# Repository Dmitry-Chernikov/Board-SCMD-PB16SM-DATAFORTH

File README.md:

# Board-SCMD-PB16SM-DATAFORTH
Board SCMD-PB16SM DATAFORTH modules MIDC5/MODC5

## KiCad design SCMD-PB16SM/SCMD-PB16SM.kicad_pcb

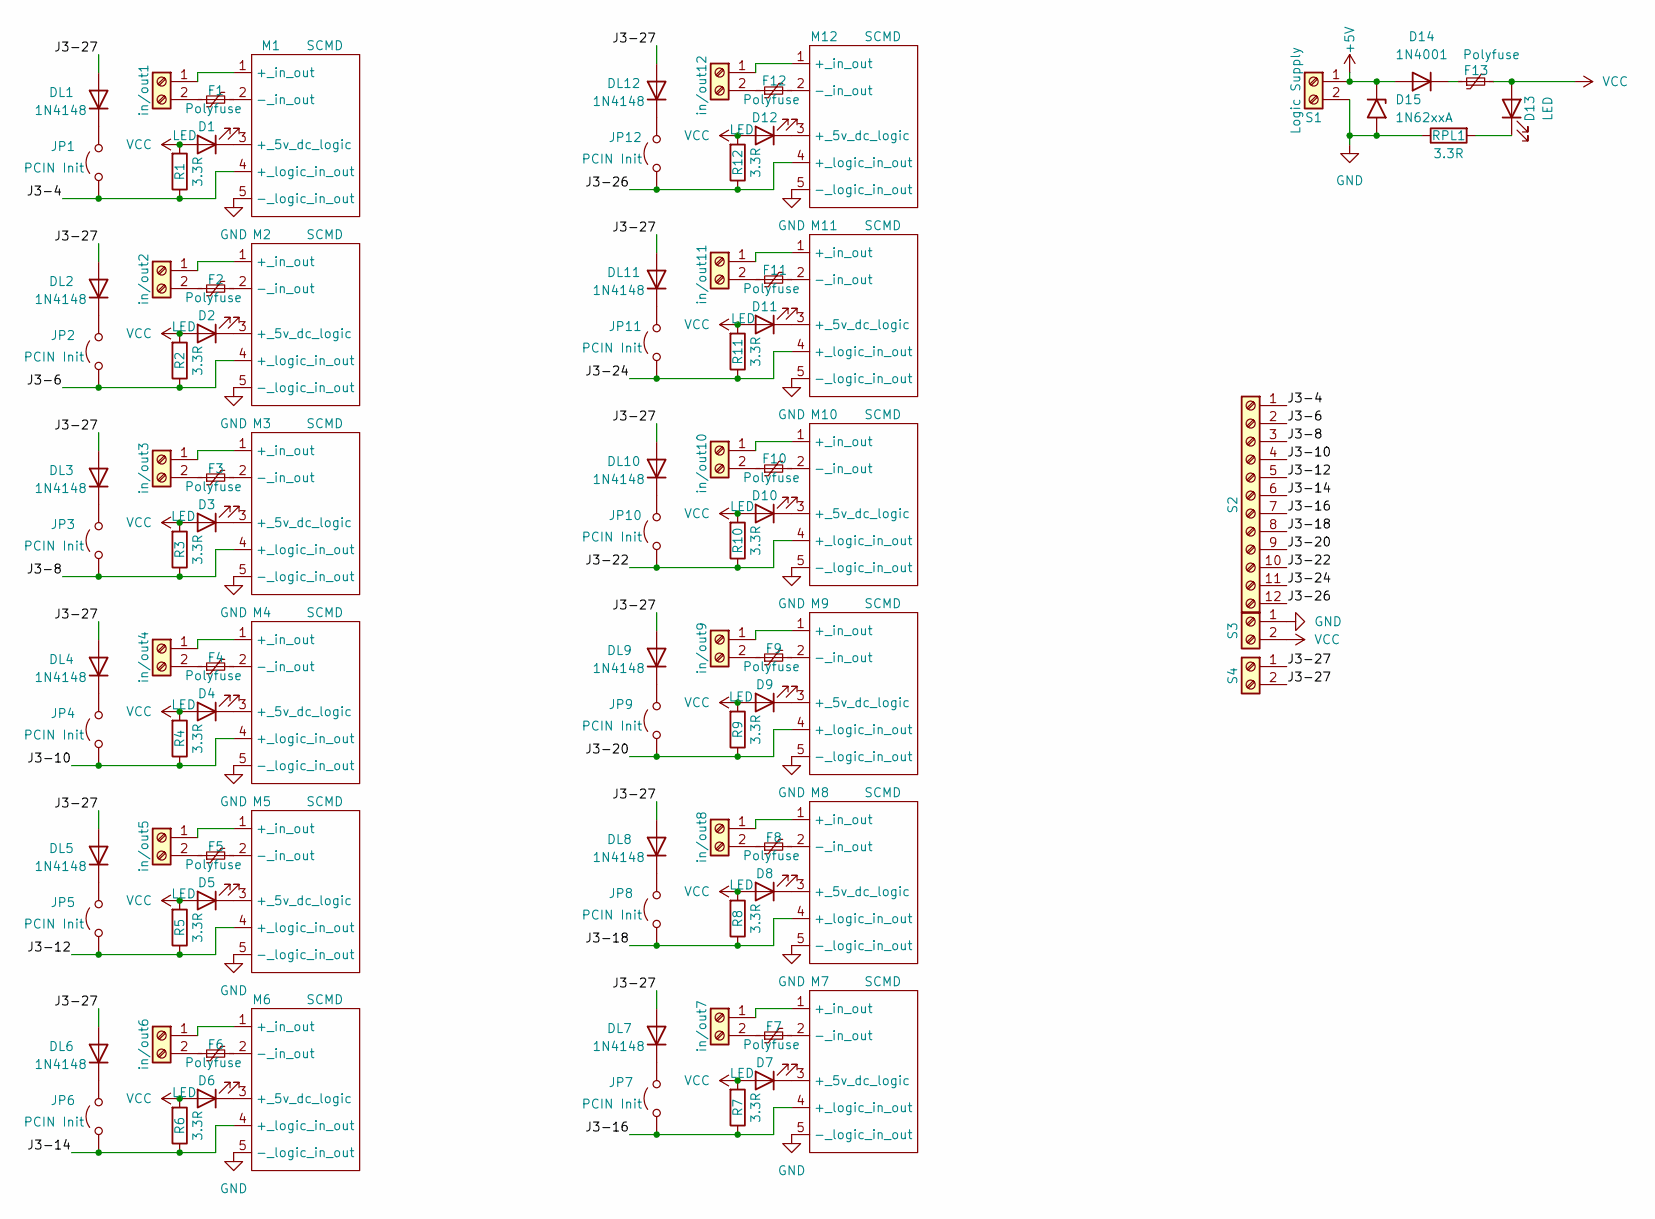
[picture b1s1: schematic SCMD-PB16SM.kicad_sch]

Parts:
D1, D2, D3, D4, D5, D6, D7, D8, D9, D10, D11, D12, D13: LED; LED_D3.0mm_Clear
D14: 1N4001; D_DO-41_SOD81_P10.16mm_Horizontal
D15: 1N62xxA; D_DO-201AE_P15.24mm_Horizontal
DL1, DL2, DL3, DL4, DL5, DL6, DL7, DL8, DL9, DL10, DL11, DL12: 1N4148; D_DO-35_SOD27_P7.62mm_Horizontal
F1, F2, F3, F4, F5, F6, F7, F8, F9, F10, F11, F12, F13: Polyfuse; Fuse_BelFuse_0ZRE0016FF_L9.9mm_W3.8mm
JP1, JP2, JP3, JP4, JP5, JP6, JP7, JP8, JP9, JP10, JP11, JP12: PCIN Init; PinHeader_1x02_P2.54mm_Vertical
M1, M2, M3, M4, M5, M6, M7, M8, M9, M10, M11, M12: SCMD; SCMD-Module-DIM
R1, R2, R3, R4, R5, R6, R7, R8, R9, R10, R11, R12: 3.3R; R_Axial_DIN0207_L6.3mm_D2.5mm_P7.62mm_Horizontal
RPL1: 3.3R; R_Axial_DIN0207_L6.3mm_D2.5mm_P7.62mm_Horizontal
S1: Logic Supply; KF141R-2.54-02P-14 (DG141R-2.54-02P-14)
S2: KF141R-2.54-12P-14; KF141R-2.54-12P-14 (DG141R-2.54-12P-14)
S3, S4: KF141R-2.54-02P-14; KF141R-2.54-02P-14 (DG141R-2.54-02P-14)
in/out1, in/out2, in/out3, in/out4, in/out5, in/out6, in/out7, in/out8, in/out9, in/out10, in/out11, in/out12: KF141R-2.54-02P-14; KF141R-2.54-02P-14 (DG141R-2.54-02P-14)

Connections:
+5V: D14.2 (A), D15.1 (A1), S1.1
/J3-4: JP1.1 (A), M1.4 (+_logic_in_out), R1.1, S2.1
/J3-6: JP2.1 (A), M2.4 (+_logic_in_out), R2.1, S2.2
/J3-8: JP3.1 (A), M3.4 (+_logic_in_out), R3.1, S2.3
/J3-10: JP4.1 (A), M4.4 (+_logic_in_out), R4.1, S2.4
/J3-12: JP5.1 (A), M5.4 (+_logic_in_out), R5.1, S2.5
/J3-14: JP6.1 (A), M6.4 (+_logic_in_out), R6.1, S2.6
/J3-16: JP7.1 (A), M7.4 (+_logic_in_out), R7.1, S2.7
/J3-18: JP8.1 (A), M8.4 (+_logic_in_out), R8.1, S2.8
/J3-20: JP9.1 (A), M9.4 (+_logic_in_out), R9.1, S2.9
/J3-22: JP10.1 (A), M10.4 (+_logic_in_out), R10.1, S2.10
/J3-24: JP11.1 (A), M11.4 (+_logic_in_out), R11.1, S2.11
/J3-26: JP12.1 (A), M12.4 (+_logic_in_out), R12.1, S2.12
/J3-27: DL1.2 (A), DL2.2 (A), DL3.2 (A), DL4.2 (A), DL5.2 (A), DL6.2 (A), DL7.2 (A), DL8.2 (A), DL9.2 (A), DL10.2 (A), DL11.2 (A), DL12.2 (A), S4.1, S4.2
GND: D15.2 (A2), M1.5 (-_logic_in_out), M2.5 (-_logic_in_out), M3.5 (-_logic_in_out), M4.5 (-_logic_in_out), M5.5 (-_logic_in_out), M6.5 (-_logic_in_out), M7.5 (-_logic_in_out), M8.5 (-_logic_in_out), M9.5 (-_logic_in_out), M10.5 (-_logic_in_out), M11.5 (-_logic_in_out), M12.5 (-_logic_in_out), RPL1.1, S1.2, S3.1
unnamed: D1.1 (K), M1.3 (+_5v_dc_logic)
unnamed: D2.1 (K), M2.3 (+_5v_dc_logic)
unnamed: D3.1 (K), M3.3 (+_5v_dc_logic)
unnamed: D4.1 (K), M4.3 (+_5v_dc_logic)
unnamed: D5.1 (K), M5.3 (+_5v_dc_logic)
unnamed: D6.1 (K), M6.3 (+_5v_dc_logic)
unnamed: D7.1 (K), M7.3 (+_5v_dc_logic)
unnamed: D8.1 (K), M8.3 (+_5v_dc_logic)
unnamed: D9.1 (K), M9.3 (+_5v_dc_logic)
unnamed: D10.1 (K), M10.3 (+_5v_dc_logic)
unnamed: D11.1 (K), M11.3 (+_5v_dc_logic)
unnamed: D12.1 (K), M12.3 (+_5v_dc_logic)
unnamed: D13.1 (K), RPL1.2
unnamed: D14.1 (K), F13.1
unnamed: DL1.1 (K), JP1.2 (B)
unnamed: DL2.1 (K), JP2.2 (B)
unnamed: DL3.1 (K), JP3.2 (B)
unnamed: DL4.1 (K), JP4.2 (B)
unnamed: DL5.1 (K), JP5.2 (B)
unnamed: DL6.1 (K), JP6.2 (B)
unnamed: DL7.1 (K), JP7.2 (B)
unnamed: DL8.1 (K), JP8.2 (B)
unnamed: DL9.1 (K), JP9.2 (B)
unnamed: DL10.1 (K), JP10.2 (B)
unnamed: DL11.1 (K), JP11.2 (B)
unnamed: DL12.1 (K), JP12.2 (B)
unnamed: M1.1 (+_in_out), in/out1.1
unnamed: F1.2, M1.2 (-_in_out)
unnamed: M2.1 (+_in_out), in/out2.1
unnamed: F2.2, M2.2 (-_in_out)
unnamed: M3.1 (+_in_out), in/out3.1
unnamed: F3.2, M3.2 (-_in_out)
unnamed: M4.1 (+_in_out), in/out4.1
unnamed: F4.2, M4.2 (-_in_out)
unnamed: M5.1 (+_in_out), in/out5.1
unnamed: F5.2, M5.2 (-_in_out)
unnamed: M6.1 (+_in_out), in/out6.1
unnamed: F6.2, M6.2 (-_in_out)
unnamed: M7.1 (+_in_out), in/out7.1
unnamed: F7.2, M7.2 (-_in_out)
unnamed: M8.1 (+_in_out), in/out8.1
unnamed: F8.2, M8.2 (-_in_out)
unnamed: M9.1 (+_in_out), in/out9.1
unnamed: F9.2, M9.2 (-_in_out)
unnamed: M10.1 (+_in_out), in/out10.1
unnamed: F10.2, M10.2 (-_in_out)
unnamed: M11.1 (+_in_out), in/out11.1
unnamed: F11.2, M11.2 (-_in_out)
unnamed: M12.1 (+_in_out), in/out12.1
unnamed: F12.2, M12.2 (-_in_out)
unnamed: F1.1, in/out1.2
unnamed: F2.1, in/out2.2
unnamed: F3.1, in/out3.2
unnamed: F4.1, in/out4.2
unnamed: F5.1, in/out5.2
unnamed: F6.1, in/out6.2
unnamed: F7.1, in/out7.2
unnamed: F8.1, in/out8.2
unnamed: F9.1, in/out9.2
unnamed: F10.1, in/out10.2
unnamed: F11.1, in/out11.2
unnamed: F12.1, in/out12.2
VCC: D1.2 (A), D2.2 (A), D3.2 (A), D4.2 (A), D5.2 (A), D6.2 (A), D7.2 (A), D8.2 (A), D9.2 (A), D10.2 (A), D11.2 (A), D12.2 (A), D13.2 (A), F13.2, R1.2, R2.2, R3.2, R4.2, R5.2, R6.2, R7.2, R8.2, R9.2, R10.2, R11.2, R12.2, S3.2

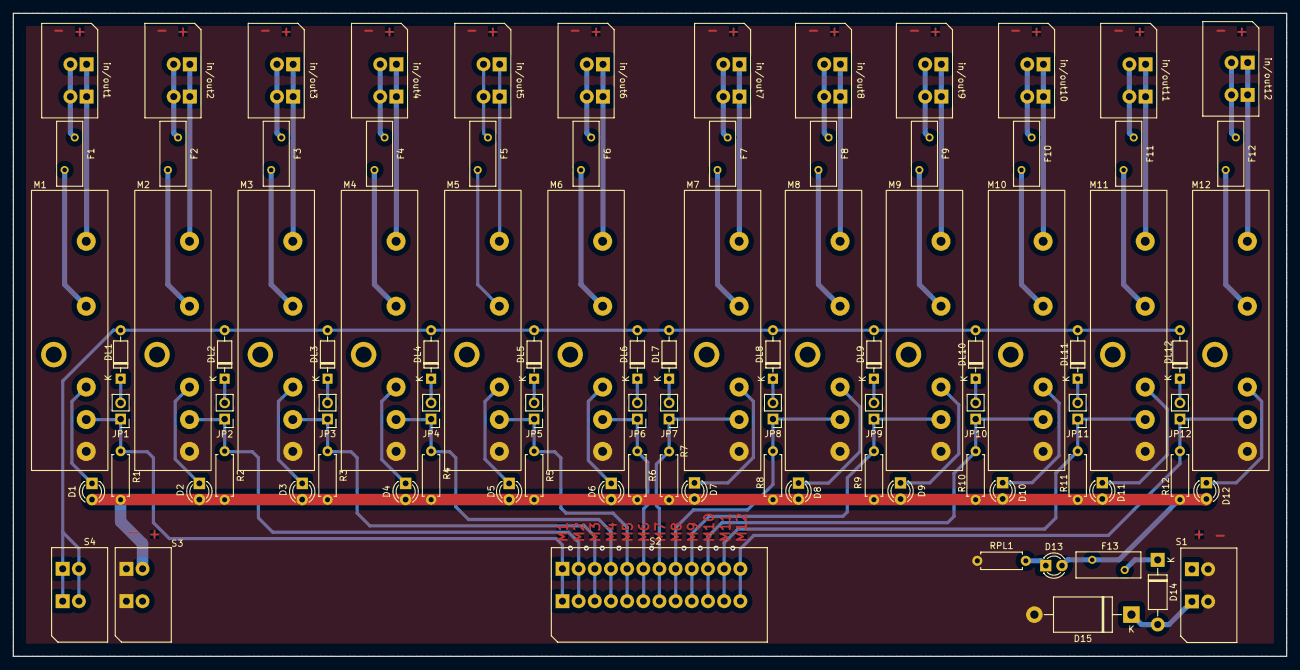
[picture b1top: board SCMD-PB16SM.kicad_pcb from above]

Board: 2 copper layers, 200.0 x 101.0 mm, 93 parts (0 on the bottom side), 78 nets.

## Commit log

2024-09-20 Add files via upload
    ADD PCINT INTERUP
